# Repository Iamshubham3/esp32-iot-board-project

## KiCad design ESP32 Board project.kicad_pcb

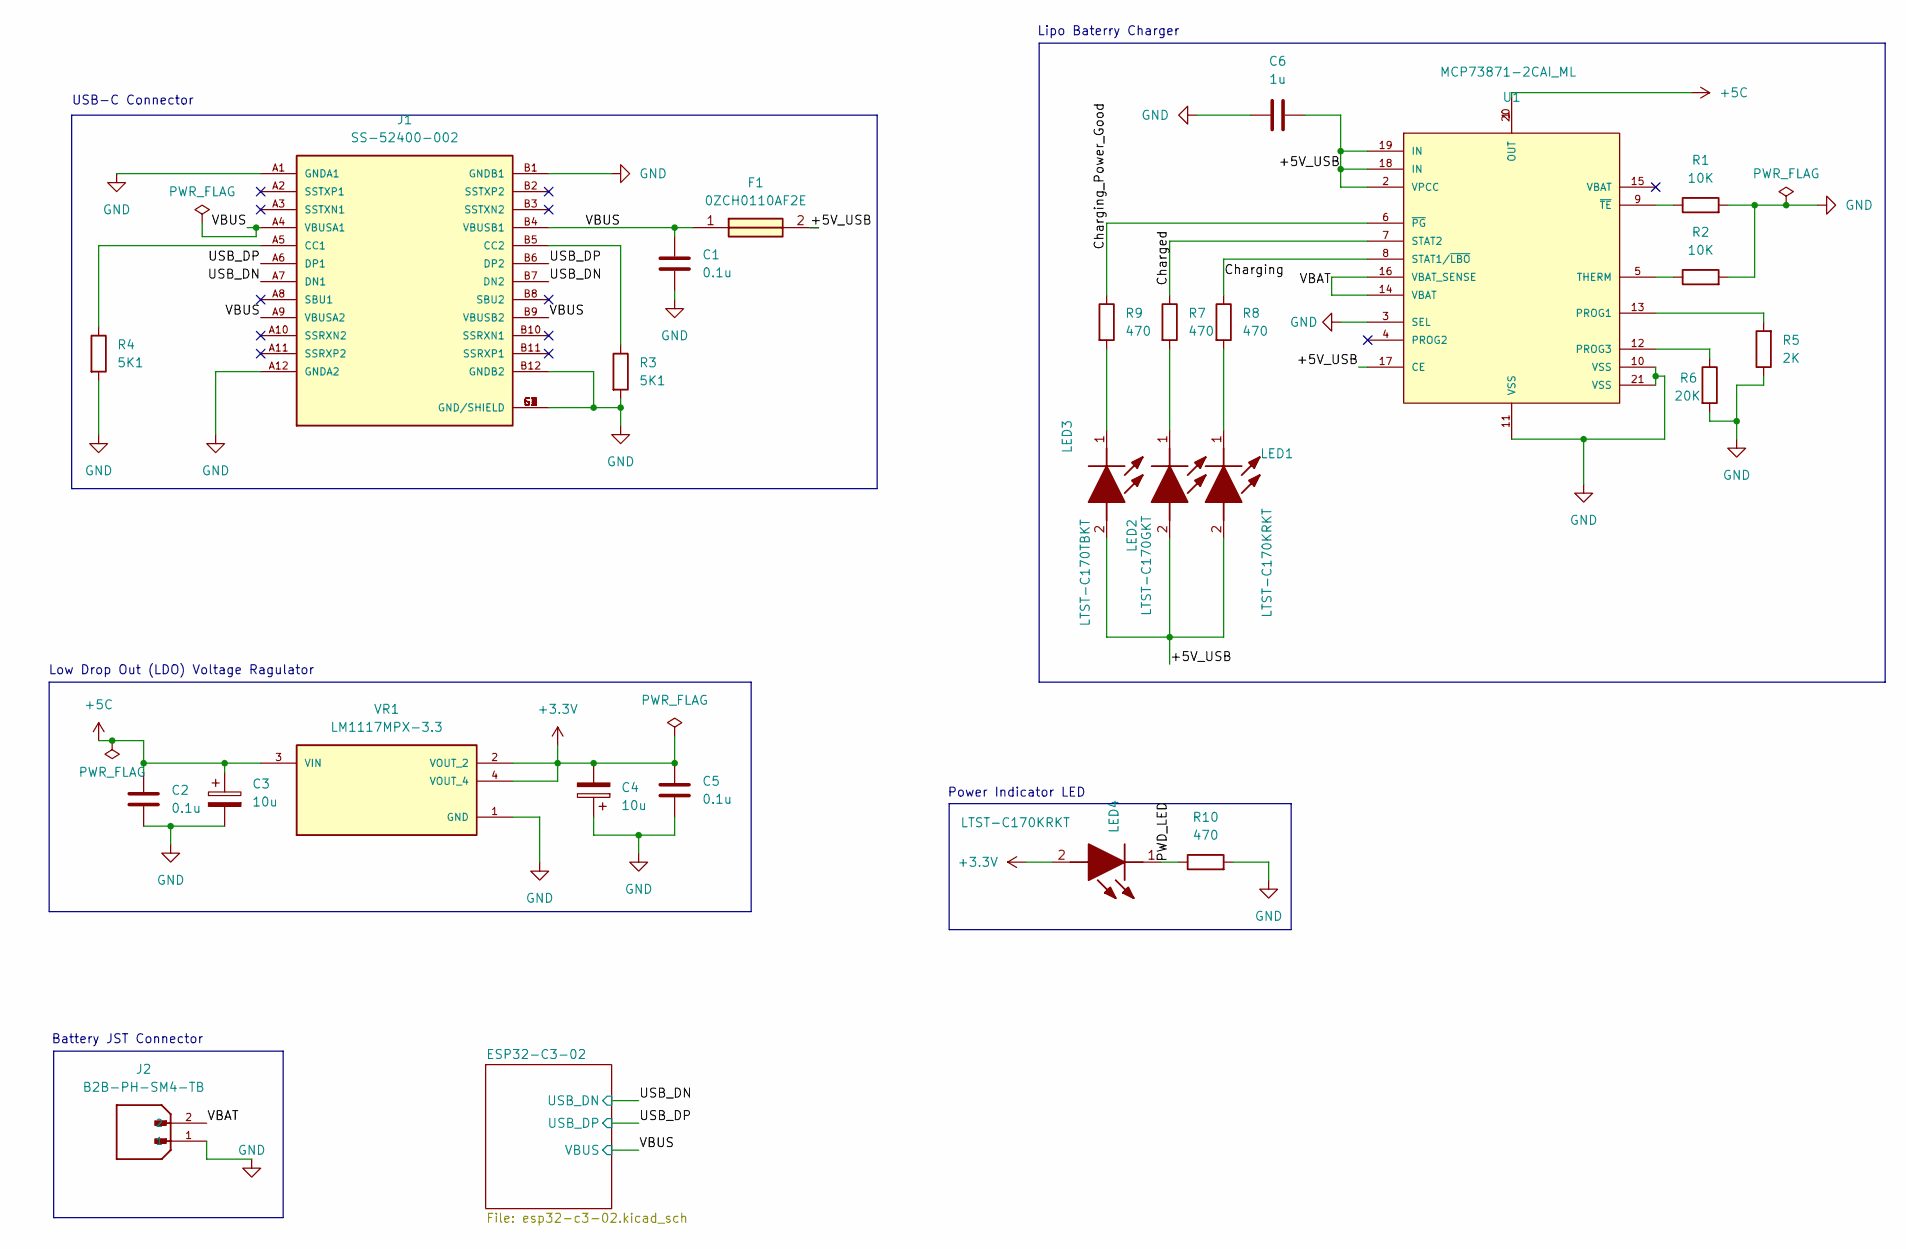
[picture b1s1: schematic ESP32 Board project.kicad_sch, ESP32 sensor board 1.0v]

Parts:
C1, C2, C5: 0.1u; C_0805_2012Metric
C3, C4: 10u; T491A
C6: 1u; C_0805_2012Metric
F1: 0ZCH0110AF2E; FUSC3226X100N; Manufacturer_Part_Number 0ZCH0110AF2E
J1: SS-52400-002; BELFUSE_SS-52400-002; PARTREV A0
J2: B2B-PH-SM4-TB; JST_B2B-PH-SM4-TB; PARTREV N/A
LED1, LED4: LTST-C170KRKT; LEDC2012X120N; Manufacturer_Part_Number LTST-C170KRKT; Mouser Part Number 859-LTST-C170KRKT
LED2: LTST-C170GKT; LEDC2012X120N; Manufacturer_Part_Number LTST-C170GKT; Mouser Part Number 859-LTST-C170GKT
LED3: LTST-C170TBKT; LEDC2012X120N; Manufacturer_Part_Number LTST-C170TBKT; Mouser Part Number 859-LTST-C170TBKT
R1, R2: 10K; R_0805_2012Metric
R3, R4: 5K1; R_0805_2012Metric
R5: 2K; R_0805_2012Metric
R6: 20K; R_0805_2012Metric
R7, R8, R9, R10: 470; R_0805_2012Metric
U1: MCP73871-2CAI_ML; QFN50P400X400X100-21N; PARTREV D
VR1: LM1117MPX-3.3; VREG_LM1117MPX-3.3

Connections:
+3.3V: C4.2, C5.2, LED4.2 (A), VR1.2 (VOUT_2), VR1.4 (VOUT_4); also elsewhere on the board
/+5V_USB: C6.2, F1.2, LED1.2 (A), LED2.2 (A), LED3.2 (A), U1.2 (VPCC), U1.17 (CE), U1.18 (IN), U1.19 (IN)
/Charged: R7.1, U1.7 (STAT2)
/Charging: R8.1, U1.8 (STAT1/~LBO)
/Charging_Power_Good: R9.1, U1.6 (~PG)
/PWD_LED: LED4.1 (K), R10.1
/USB_DN: J1.A7 (DN1), J1.B7 (DN2); also elsewhere on the board
/USB_DP: J1.A6 (DP1), J1.B6 (DP2); also elsewhere on the board
/VBAT: J2.2, U1.14 (VBAT), U1.16 (VBAT_SENSE)
/VBUS: C1.1, F1.1, J1.A4 (VBUSA1), J1.A9 (VBUSA2), J1.B4 (VBUSB1), J1.B9 (VBUSB2); also elsewhere on the board
GND: C1.2, C2.2, C3.2, C4.1, C5.1, C6.1, J1.A1 (GNDA1), J1.A12 (GNDA2), J1.B1 (GNDB1), J1.B12 (GNDB2), J1.G1 (GND/SHIELD), J1.G2 (GND/SHIELD), J1.G3 (GND/SHIELD), J1.G4 (GND/SHIELD), J1.S1 (GND/SHIELD), J1.S2 (GND/SHIELD), J1.S3 (GND/SHIELD), J1.S4 (GND/SHIELD), J2.1, R1.2, R2.2, R3.2, R4.2, R5.1, R6.2, R10.2, U1.3 (SEL), U1.10 (VSS), U1.11 (VSS), U1.21 (VSS), VR1.1 (GND); also elsewhere on the board
unnamed: J1.A5 (CC1), R4.1
unnamed: J1.B5 (CC2), R3.1
unnamed: LED1.1 (K), R8.2
unnamed: LED2.1 (K), R7.2
unnamed: LED3.1 (K), R9.2
unnamed: R5.2, U1.13 (PROG1)
unnamed: R6.1, U1.12 (PROG3)
unnamed: R2.1, U1.5 (THERM)
unnamed: R1.1, U1.9 (~TE)

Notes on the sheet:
Power Indicator LED
Lipo Baterry Charger
Battery JST Connector
USB-C Connector
Low Drop Out (LDO) Voltage Ragulator

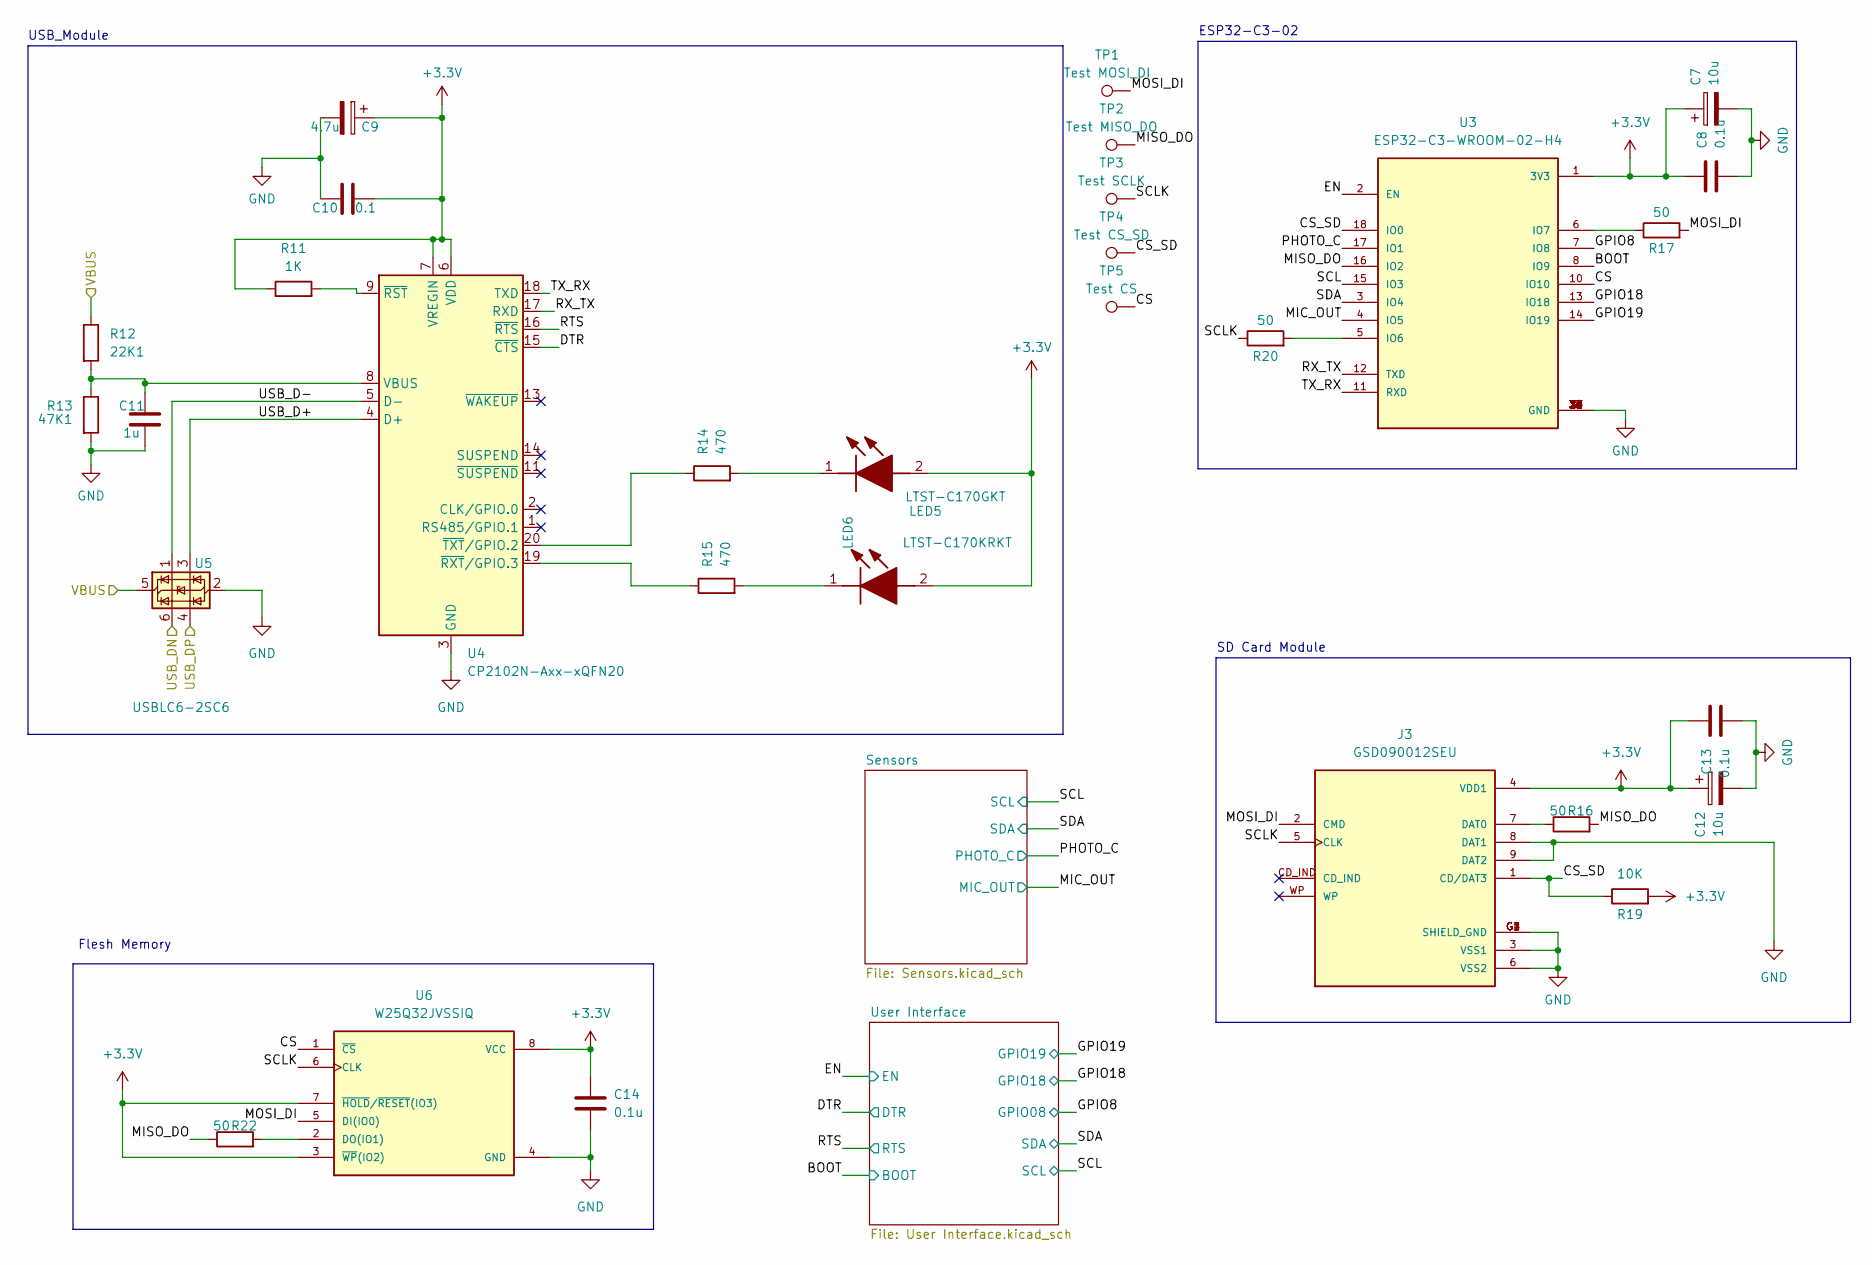
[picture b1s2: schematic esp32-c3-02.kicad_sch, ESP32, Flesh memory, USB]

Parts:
C7, C12: 10u; T491A
C8, C13, C14: 0.1u; C_0805_2012Metric
C9: 4.7u; T491A
C10: 0.1; C_0805_2012Metric
C11: 1u; C_0805_2012Metric
J3: GSD090012SEU; AMPHENOL_GSD090012SEU; PARTREV E
LED5: LTST-C170GKT; LEDC2012X120N; Manufacturer_Part_Number LTST-C170GKT; Mouser Part Number 859-LTST-C170GKT
LED6: LTST-C170KRKT; LEDC2012X120N; Manufacturer_Part_Number LTST-C170KRKT; Mouser Part Number 859-LTST-C170KRKT
R11: 1K; R_0805_2012Metric
R12: 22K1; R_0805_2012Metric
R13: 47K1; R_0805_2012Metric
R14, R15: 470; R_0805_2012Metric
R16, R17, R20, R22: 50; R_0805_2012Metric
R19: 10K; R_0805_2012Metric
TP1: Test MOSI_DI; TestPoint_Pad_D1.0mm
TP2: Test MISO_DO; TestPoint_Pad_D1.0mm
TP3: Test SCLK; TestPoint_Pad_D1.0mm
TP4: Test CS_SD; TestPoint_Pad_D1.0mm
TP5: Test CS; TestPoint_Pad_D1.0mm
U3: ESP32-C3-WROOM-02-H4; MODULE_ESP32-C3-WROOM-02-H4
U4: CP2102N-Axx-xQFN20; SiliconLabs_QFN-20-1EP_3x3mm_P0.5mm_EP1.8x1.8mm
U5: USBLC6-2SC6; SOT-23-6
U6: W25Q32JVSSIQ; SOIC127P790X216-8N; M_PART_NUMBER W25QXX

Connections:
+3.3V: C7.1, C8.1, C9.1, C10.1, C12.1, C13.1, C14.1, J3.4 (VDD1), LED5.2 (A), LED6.2 (A), R11.1, R19.2, U3.1 (3V3), U4.6 (VDD), U4.7 (VREGIN), U6.3 (~WP(IO2)), U6.7 (~HOLD/~RESET(IO3)), U6.8 (VCC); also elsewhere on the board
/ESP32-C3-02/BOOT: U3.8 (IO9); also elsewhere on the board
/ESP32-C3-02/CS: TP5.1, U3.10 (IO10), U6.1 (~CS)
/ESP32-C3-02/CS_SD: J3.1 (CD/DAT3), R19.1, TP4.1, U3.18 (IO0)
/ESP32-C3-02/DTR: U4.15 (~CTS); also elsewhere on the board
/ESP32-C3-02/EN: U3.2 (EN); also elsewhere on the board
/ESP32-C3-02/GPIO8: U3.7 (IO8); also elsewhere on the board
/ESP32-C3-02/GPIO18: U3.13 (IO18); also elsewhere on the board
/ESP32-C3-02/GPIO19: U3.14 (IO19); also elsewhere on the board
/ESP32-C3-02/MIC_OUT: U3.4 (IO5); also elsewhere on the board
/ESP32-C3-02/MISO_DO: R16.2, R22.1, TP2.1, U3.16 (IO2)
/ESP32-C3-02/MOSI_DI: J3.2 (CMD), R17.2, TP1.1, U6.5 (DI(IO0))
/ESP32-C3-02/PHOTO_C: U3.17 (IO1); also elsewhere on the board
/ESP32-C3-02/RTS: U4.16 (~RTS); also elsewhere on the board
/ESP32-C3-02/RX_TX: U3.12 (TXD), U4.17 (RXD)
/ESP32-C3-02/SCL: U3.15 (IO3); also elsewhere on the board
/ESP32-C3-02/SCLK: J3.5 (CLK), R20.1, TP3.1, U6.6 (CLK)
/ESP32-C3-02/SDA: U3.3 (IO4); also elsewhere on the board
/ESP32-C3-02/TX_RX: U3.11 (RXD), U4.18 (TXD)
/ESP32-C3-02/USB_D+: U4.4 (D+), U5.3 (I/O2)
/ESP32-C3-02/USB_D-: U4.5 (D-), U5.1 (I/O1)
/USB_DN: U5.6 (I/O1); also elsewhere on the board
/USB_DP: U5.4 (I/O2); also elsewhere on the board
/VBUS: R12.1, U5.5 (VBUS); also elsewhere on the board
GND: C7.2, C8.2, C9.2, C10.2, C11.2, C12.2, C13.2, C14.2, J3.3 (VSS1), J3.6 (VSS2), J3.8 (DAT1), J3.9 (DAT2), J3.G1 (SHIELD_GND), J3.G2 (SHIELD_GND), J3.G3 (SHIELD_GND), J3.G4 (SHIELD_GND), R13.2, U3.9 (GND), U3.19 (GND), U3.20 (GND), U3.21 (GND), U3.22 (GND), U3.23 (GND), U3.24 (GND), U3.25 (GND), U3.26 (GND), U3.27 (GND), U3.28 (GND), U3.29 (GND), U3.30 (GND), U3.31 (GND), U3.32 (GND), U3.33 (GND), U3.34 (GND), U3.35 (GND), U3.36 (GND), U3.37 (GND), U3.38 (GND), U3.39 (GND), U4.3 (GND), U4.12 (GND), U4.21 (GND), U5.2 (GND), U6.4 (GND); also elsewhere on the board
unnamed: J3.7 (DAT0), R16.1
unnamed: LED5.1 (K), R14.2
unnamed: LED6.1 (K), R15.2
unnamed: R20.2, U3.5 (IO6)
unnamed: R17.1, U3.6 (IO7)
unnamed: C11.1, R12.2, R13.1, U4.8 (VBUS)
unnamed: R11.2, U4.9 (~RST)
unnamed: R15.1, U4.19 (~RXT/GPIO.3)
unnamed: R14.1, U4.20 (~TXT/GPIO.2)
unnamed: R22.2, U6.2 (DO(IO1))

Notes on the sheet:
Flesh Memory
SD Card Module
USB_Module
ESP32-C3-02

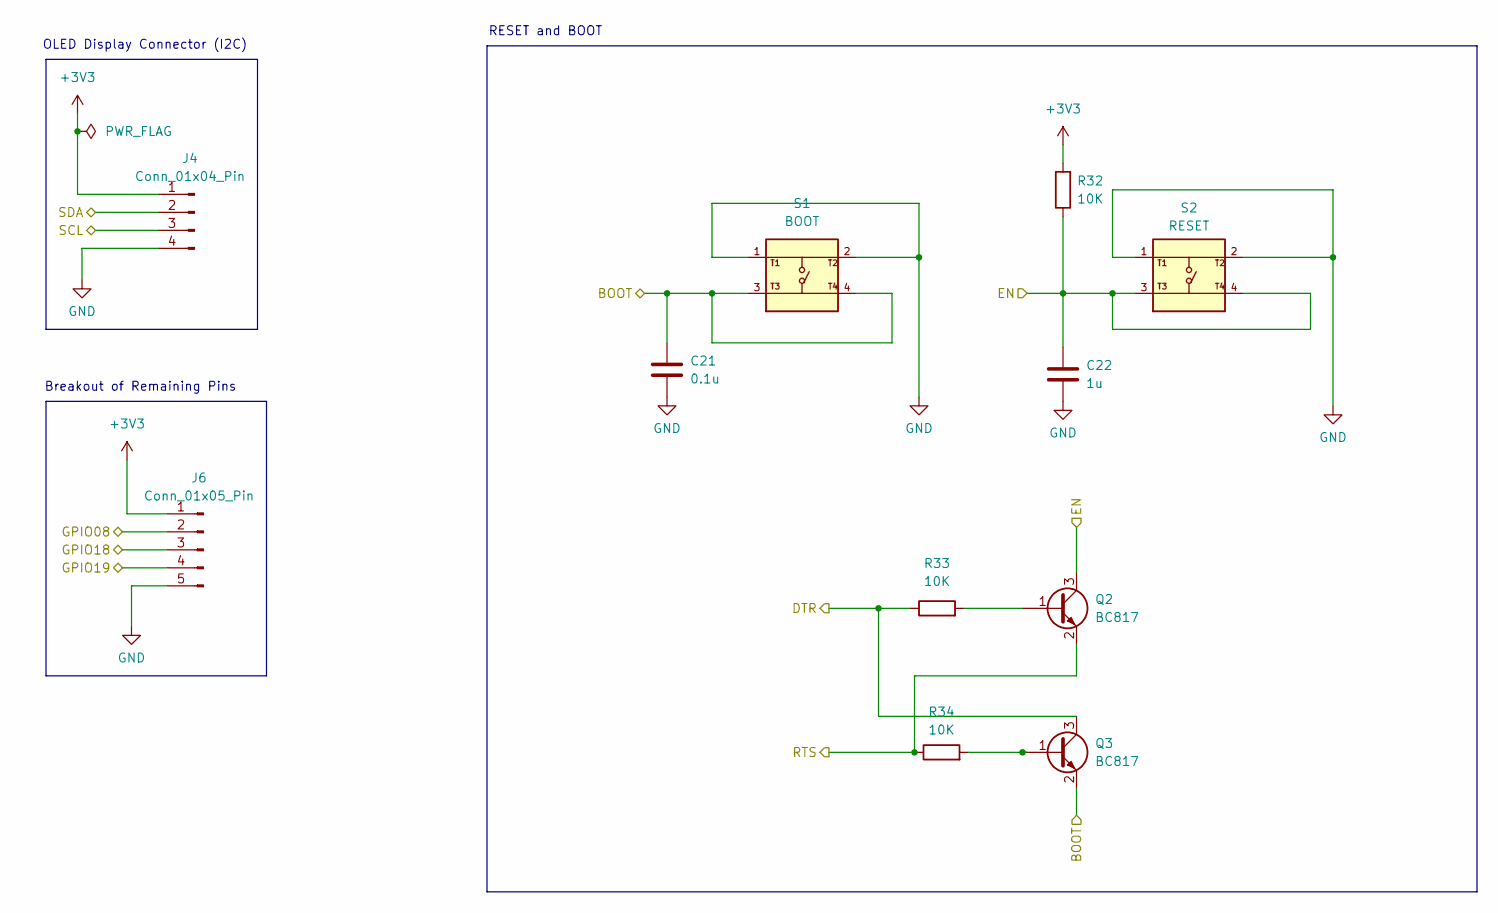
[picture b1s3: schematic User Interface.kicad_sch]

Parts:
C21: 0.1u; C_0805_2012Metric
C22: 1u; C_0805_2012Metric
J4: Conn_01x04_Pin; PinSocket_1x04_P2.54mm_Vertical
J6: Conn_01x05_Pin; PinSocket_1x05_P2.54mm_Vertical
Q2, Q3: BC817; SOT-23
R32, R33, R34: 10K; R_0805_2012Metric
S1: BOOT; SW_USLPT2819DT2TR; PARTREV P
S2: RESET; SW_USLPT2819DT2TR; PARTREV P

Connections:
+3V3: J4.1, J6.1, R32.2
/ESP32-C3-02/BOOT: C21.1, Q3.2 (E), S1.3, S1.4; also elsewhere on the board
/ESP32-C3-02/DTR: Q3.3 (C), R33.1; also elsewhere on the board
/ESP32-C3-02/EN: C22.1, Q2.3 (C), R32.1, S2.3, S2.4; also elsewhere on the board
/ESP32-C3-02/GPIO8: J6.2; also elsewhere on the board
/ESP32-C3-02/GPIO18: J6.3; also elsewhere on the board
/ESP32-C3-02/GPIO19: J6.4; also elsewhere on the board
/ESP32-C3-02/RTS: Q2.2 (E), R34.1; also elsewhere on the board
/ESP32-C3-02/SCL: J4.3; also elsewhere on the board
/ESP32-C3-02/SDA: J4.2; also elsewhere on the board
GND: C21.2, C22.2, J4.4, J6.5, S1.1, S1.2, S2.1, S2.2; also elsewhere on the board
unnamed: Q2.1 (B), R33.2
unnamed: Q3.1 (B), R34.2

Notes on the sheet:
RESET and BOOT
OLED Display Connector (I2C)
Breakout of Remaining Pins

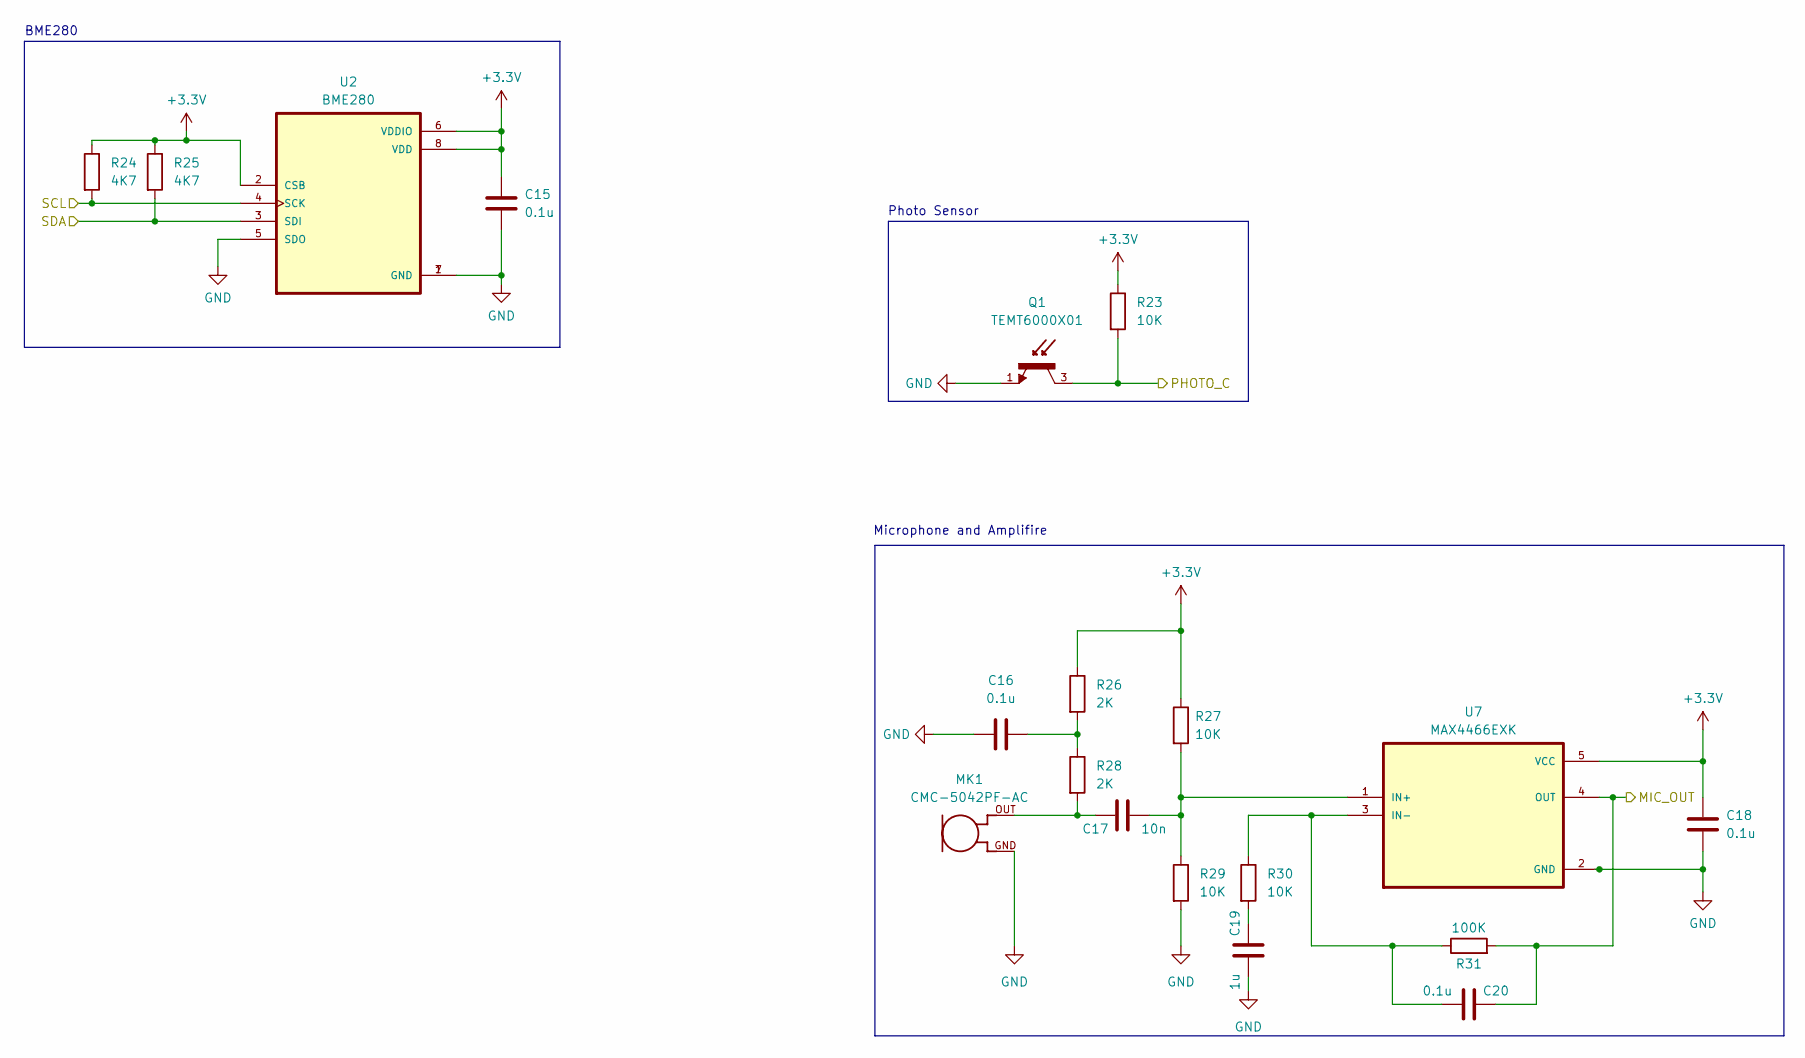
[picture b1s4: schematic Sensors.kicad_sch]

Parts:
C15, C16, C18, C20: 0.1u; C_0805_2012Metric
C17: 10n; C_0805_2012Metric
C19: 1u; C_0805_2012Metric
MK1: CMC-5042PF-AC; CUI_CMC-5042PF-AC
Q1: TEMT6000X01; TRANS_TEMT6000X01; PARTREV 1.9
R23, R27, R29, R30: 10K; R_0805_2012Metric
R24, R25: 4K7; R_0805_2012Metric
R26, R28: 2K; R_0805_2012Metric
R31: 100K; R_0805_2012Metric
U2: BME280; PSON65P250X250X100-8N
U7: MAX4466EXK; SOT65P210X110-5N

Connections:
+3.3V: C15.1, C18.1, R23.1, R24.1, R25.1, R26.1, R27.1, U2.2 (CSB), U2.6 (VDDIO), U2.8 (VDD), U7.5 (VCC); also elsewhere on the board
/ESP32-C3-02/MIC_OUT: C20.1, R31.2, U7.4 (OUT); also elsewhere on the board
/ESP32-C3-02/PHOTO_C: Q1.3, R23.2; also elsewhere on the board
/ESP32-C3-02/SCL: R24.2, U2.4 (SCK); also elsewhere on the board
/ESP32-C3-02/SDA: R25.2, U2.3 (SDI); also elsewhere on the board
GND: C15.2, C16.1, C18.2, C19.2, MK1.GND, Q1.1, R29.2, U2.1 (GND), U2.5 (SDO), U2.7 (GND), U7.2 (GND); also elsewhere on the board
unnamed: C16.2, R26.2, R28.1
unnamed: C17.1, MK1.OUT, R28.2
unnamed: C19.1, R30.2
unnamed: C17.2, R27.2, R29.1, U7.1 (IN+)
unnamed: C20.2, R30.1, R31.1, U7.3 (IN-)

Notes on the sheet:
Microphone and Amplifire
BME280
Photo Sensor

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
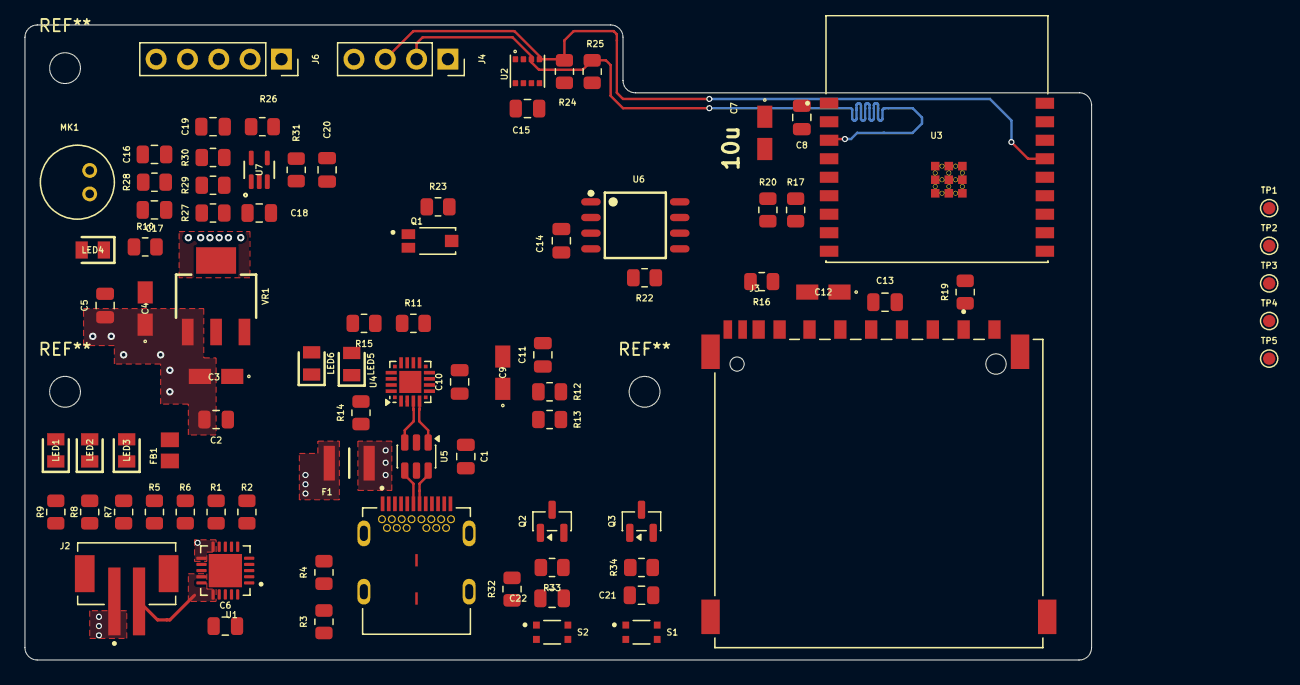
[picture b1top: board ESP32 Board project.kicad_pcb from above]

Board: 4 copper layers, 86.5 x 51.5 mm, 86 parts (0 on the bottom side), 60 nets.

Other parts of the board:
FB1: FBMJ2125HM330-T; BEADC2012X105N

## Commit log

2026-02-27 Initial commit: KiCad project (WIP)
2026-03-02 PCB: added copper zones
2026-03-12 Updated SPI connection and +5V connection
